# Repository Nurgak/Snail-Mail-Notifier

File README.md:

# Snail Mail Notifier

The Snail Mail Notifier is a small module based on a one-way transmitter-receiver pair and [ATtiny85](http://www.atmel.com/devices/attiny85.aspx) microcontrollers, it's purpose is to inform a user of the arrival of regular mail as soon as the mailbox lid has been opened. The receiver can notify the user via a buzzer, a blinking LED or transmit data to a computer that can forward an e-mail.

[The project development is documented on Hackaday.io](https://hackaday.io/project/1954-snail-mail-notifier).

## License

The Snail Mail Notifier is published under [Creative Commons Attribution license](http://creativecommons.org/licenses/by/3.0/).

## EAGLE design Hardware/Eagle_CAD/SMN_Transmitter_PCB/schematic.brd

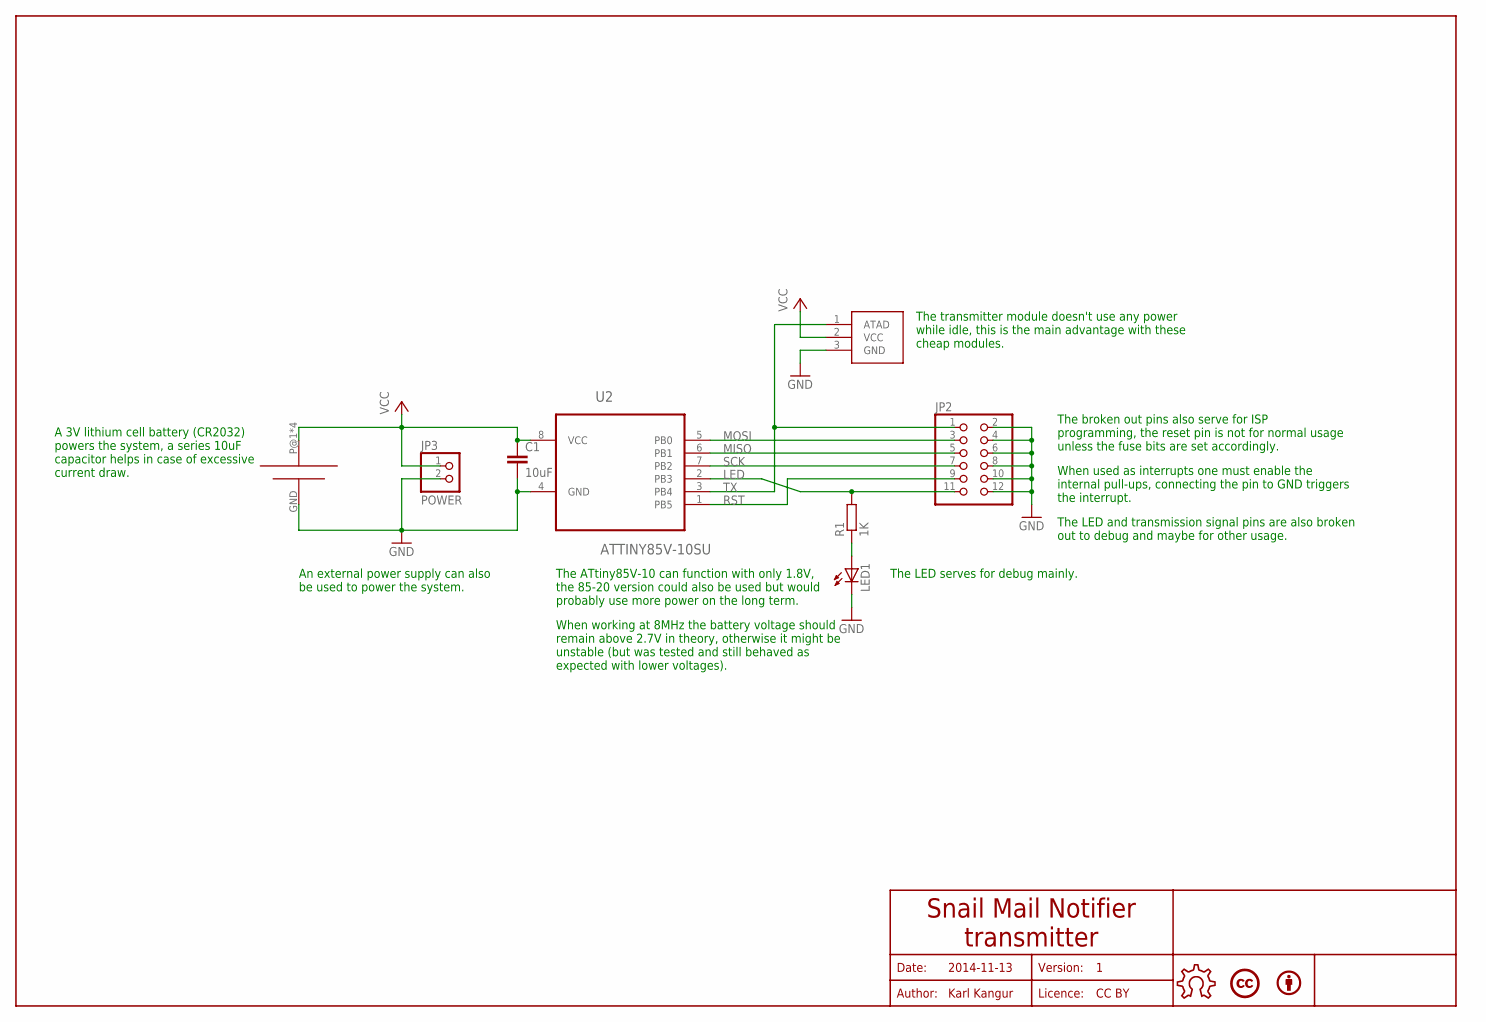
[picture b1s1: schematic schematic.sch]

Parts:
BY1: BYBOTTOM; BY
C1: 10uF; C0805
JP2: PINHD-2X6; 2X06
JP3: POWER; 1X02
LED1: LEDCHIPLED_0805; CHIPLED_0805
LICENCE1: LICENCECC-BOTTOM; CREATIVE-COMMONS
R1: 1K; R0805
U2: ATTINY85V-10SU; SOIC127P798X216-8N
U$1: RF_LINK_TRANSMITTER
U$2: CR2032-BATTERY-HOLDER; CR2032-BATTERY-HOLDER-PCB
U$5: OPEN-HARDWARE-LOGOBOTTOM-SMALL; OPEN-HARDWARE-BOTTOM-SMALL

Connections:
GND: C1.2, JP2.2, JP2.4, JP2.6, JP2.8, JP2.10, JP2.12, JP3.2, LED1.C, U2.4 (GND), U$1.3 (GND), U$2.GND (N)
LED: JP2.11, R1.2, U2.2 (PB3)
MISO: JP2.5, U2.6 (PB1)
MOSI: JP2.3, U2.5 (PB0)
unnamed: LED1.A, R1.1
RST: JP2.9, U2.1 (PB5)
SCK: JP2.7, U2.7 (PB2)
TX: JP2.1, U2.3 (PB4), U$1.1 (ATAD)
VCC: C1.1, JP3.1, U2.8 (VCC), U$1.2 (VCC), U$2.P@1, U$2.P@2, U$2.P@3, U$2.P@4

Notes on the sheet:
Date:
Author:
Licence:
Version:
2014-11-13
Karl Kangur
CC BY
Snail Mail Notifier transmitter
The ATtiny85V-10 can function with only 1.8V, the 85-20 version could also be used but would probably use more power on the long term.
The broken out pins also serve for ISP programming, the reset pin is not for normal usage unless the fuse bits are set accordingly.
A 3V lithium cell battery (CR2032) powers the system, a series 10uF capacitor helps in case of excessive current draw.
An external power supply can also be used to power the system.
The transmitter module doesn't use any power while idle, this is the main advantage with these cheap modules.
When used as interrupts one must enable the internal pull-ups, connecting the pin to GND triggers the interrupt.
The LED serves for debug mainly.
When working at 8MHz the battery voltage should remain above 2.7V in theory, otherwise it might be unstable (but was tested and still behaved as expected with lower voltages).
The LED and transmission signal pins are also broken out to debug and maybe for other usage.

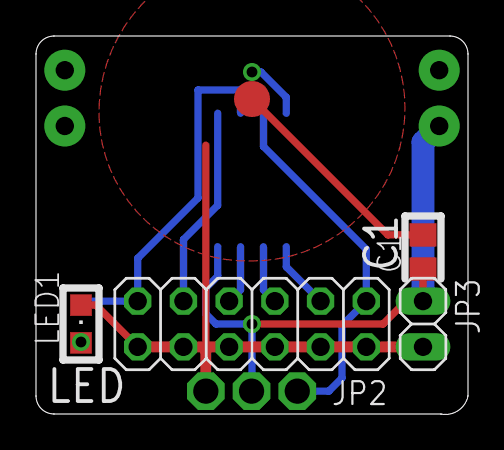
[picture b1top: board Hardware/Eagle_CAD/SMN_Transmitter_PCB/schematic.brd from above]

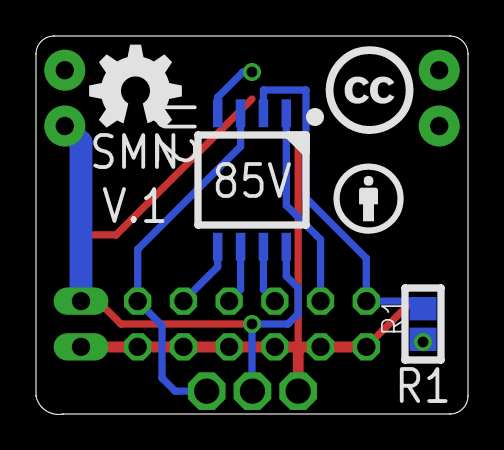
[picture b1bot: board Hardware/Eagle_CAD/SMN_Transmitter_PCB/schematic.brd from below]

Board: 2 copper layers, 24.0 x 21.0 mm, 11 parts (3 on the bottom side), 9 nets.

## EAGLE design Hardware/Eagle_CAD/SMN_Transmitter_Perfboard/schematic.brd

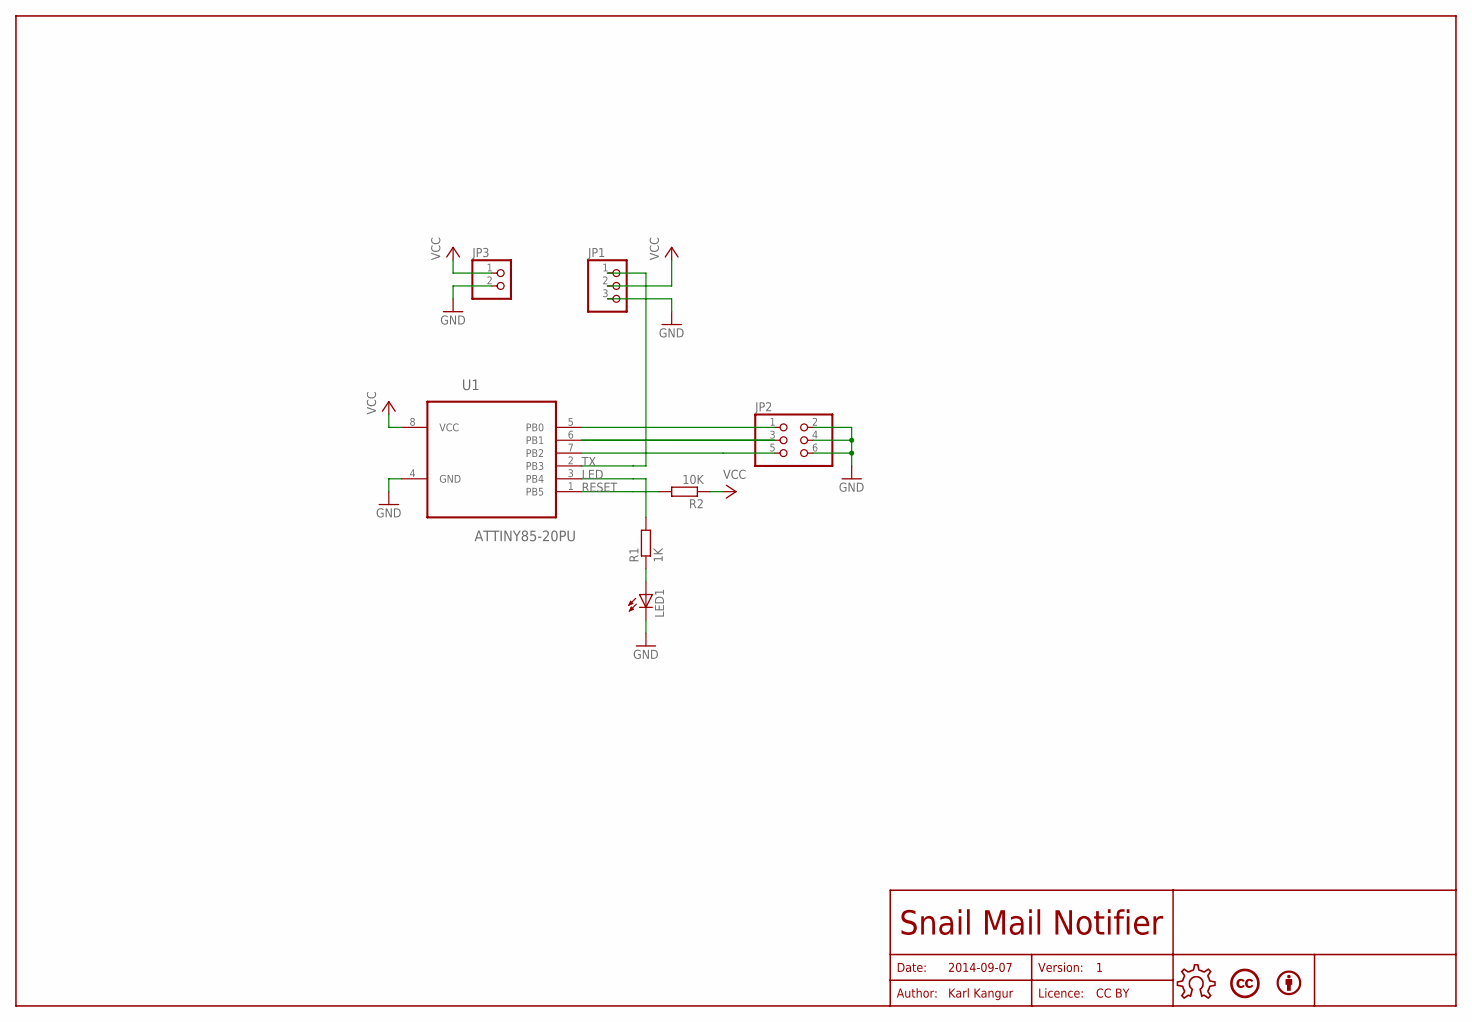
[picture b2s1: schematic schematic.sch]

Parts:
BY1: BYBOTTOM; BY
JP1: PINHD-1X3; 1X03
JP2: PINHD-2X3; 2X03
JP3: PINHD-1X2/90; 1X02/90
LED1: LED3MM
LICENCE1: LICENCECC-BOTTOM; CREATIVE-COMMONS
R1: 1K; R0805
R2: 10K; R0805
U1: ATTINY85-20PU; DIP254P762X533-8
U$5: OPEN-HARDWARE-LOGOBOTTOM-SMALL; OPEN-HARDWARE-BOTTOM-SMALL

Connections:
GND: JP1.3, JP2.2, JP2.4, JP2.6, JP3.2, LED1.K (C)
LED: R1.2, U1.3 (PB4)
unnamed: LED1.A, R1.1
unnamed: JP2.1, U1.5 (PB0)
unnamed: JP2.3, U1.6 (PB1)
unnamed: JP2.5, U1.7 (PB2)
RESET: R2.2, U1.1 (PB5)
TX: JP1.1, U1.2 (PB3)
VCC: JP1.2, JP3.1, R2.1, U1.8 (VCC)

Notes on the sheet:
Date:
Author:
Licence:
Version:
2014-09-07
Karl Kangur
CC BY
Snail Mail Notifier

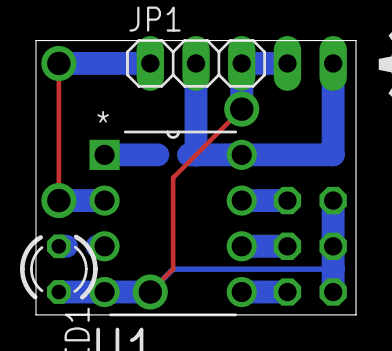
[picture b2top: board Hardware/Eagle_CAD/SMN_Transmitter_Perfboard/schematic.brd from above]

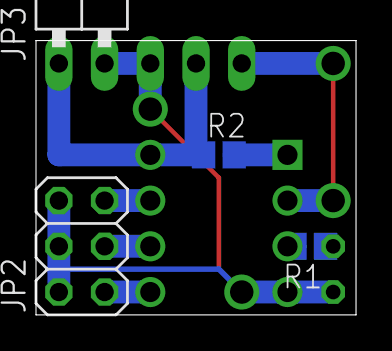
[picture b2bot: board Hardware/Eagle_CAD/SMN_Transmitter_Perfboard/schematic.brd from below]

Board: 2 copper layers, 17.8 x 15.2 mm, 10 parts (7 on the bottom side), 9 nets.

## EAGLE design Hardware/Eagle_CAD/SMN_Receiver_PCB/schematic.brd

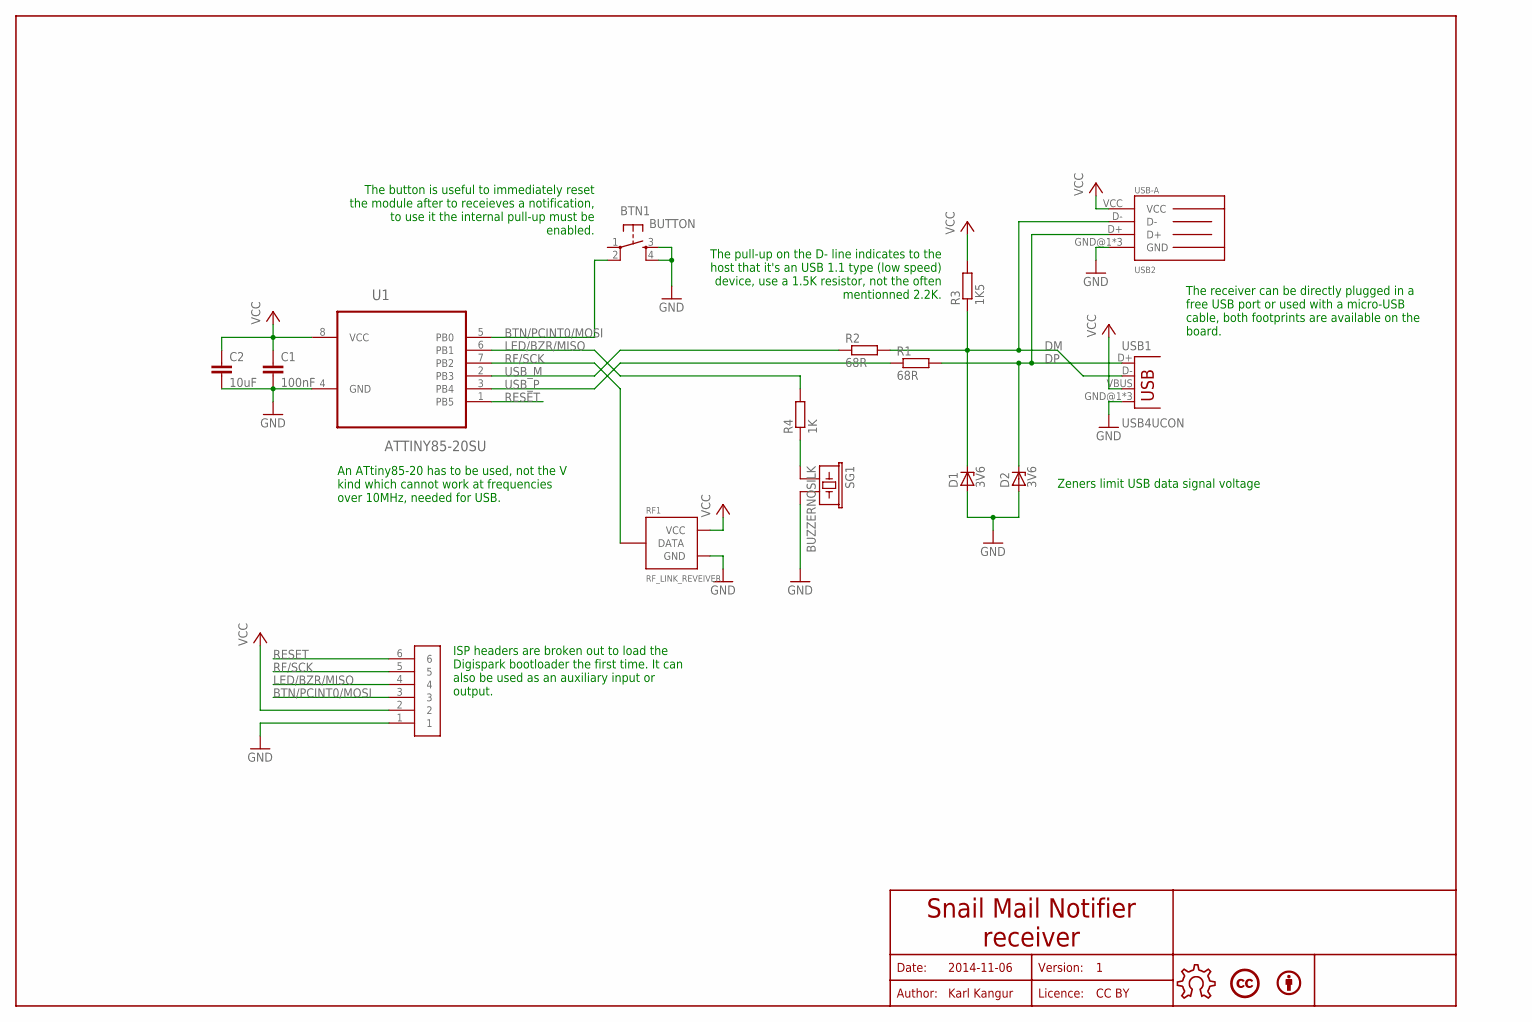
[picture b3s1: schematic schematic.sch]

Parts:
BTN1: BUTTON
BY1: BYBOTTOM; BY
C1: 100nF; C0805
C2: 10uF; C0805
D1, D2: 3V6; SOD80C
LICENCE1: LICENCECC-BOTTOM; CREATIVE-COMMONS
PIN1: PINS-6
R1, R2: 68R; R0805
R3: 1K5; R0805
R4: 1K; R0805
RF1: RF_LINK_REVEIVER
SG1: BUZZERNOSILK; PS1240P02BT-NOSILK
U1: ATTINY85-20SU; SOIC127P798X216-8N
U$5: OPEN-HARDWARE-LOGOBOTTOM-SMALL; OPEN-HARDWARE-BOTTOM-SMALL
USB1: USB4UCON; USB-MICROB-4UCON
USB2: USB-A

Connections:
BTN/PCINT0/MOSI: BTN1.2, PIN1.3, U1.5 (PB0)
DM: D1.C, R2.2, R3.1, USB1.D-, USB2.D-
DP: D2.C, R1.2, USB1.D+, USB2.D+
GND: BTN1.3, BTN1.4, C1.2, C2.2, D1.A, D2.A, PIN1.1, RF1.GND, SG1.P$2 (2), U1.4 (GND), USB1.GND@1 (GND), USB1.GND@4 (GND), USB1.GND@5 (GND), USB2.GND@1 (GND), USB2.GND@2 (GND), USB2.GND@3 (GND)
LED/BZR/MISO: PIN1.4, R4.2, U1.6 (PB1)
unnamed: R4.1, SG1.P$1 (1)
RESET: PIN1.6, U1.1 (PB5)
RF/SCK: PIN1.5, RF1.DATA@1 (DATA), RF1.DATA@2 (DATA), U1.7 (PB2)
USB_M: R2.1, U1.2 (PB3)
USB_P: R1.1, U1.3 (PB4)
VCC: C1.1, C2.1, PIN1.2, R3.2, RF1.VCC, U1.8 (VCC), USB1.VBUS, USB2.VCC

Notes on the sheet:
Date:
Author:
Licence:
Version:
2014-11-06
Karl Kangur
CC BY
Snail Mail Notifier receiver
The receiver can be directly plugged in a free USB port or used with a micro-USB cable, both footprints are available on the board.
Zeners limit USB data signal voltage
The pull-up on the D- line indicates to the host that it's an USB 1.1 type (low speed) device, use a 1.5K resistor, not the often mentionned 2.2K.
The button is useful to immediately reset the module after to receieves a notification, to use it the internal pull-up must be enabled.
An ATtiny85-20 has to be used, not the V kind which cannot work at frequencies over 10MHz, needed for USB.
ISP headers are broken out to load the Digispark bootloader the first time. It can also be used as an auxiliary input or output.

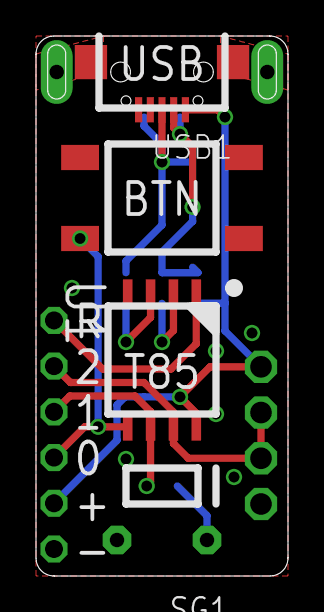
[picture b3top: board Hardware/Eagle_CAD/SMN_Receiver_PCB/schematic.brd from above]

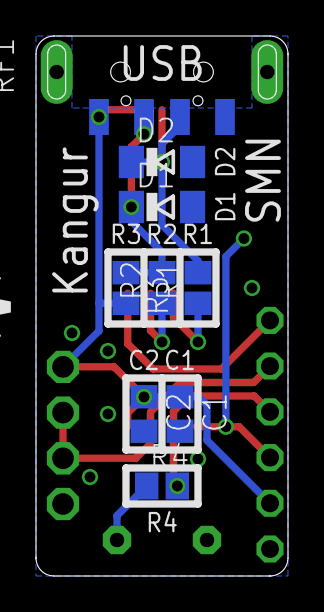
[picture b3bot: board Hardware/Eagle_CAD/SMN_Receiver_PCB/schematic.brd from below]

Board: 2 copper layers, 14.0 x 30.0 mm, 18 parts (12 on the bottom side), 11 nets.

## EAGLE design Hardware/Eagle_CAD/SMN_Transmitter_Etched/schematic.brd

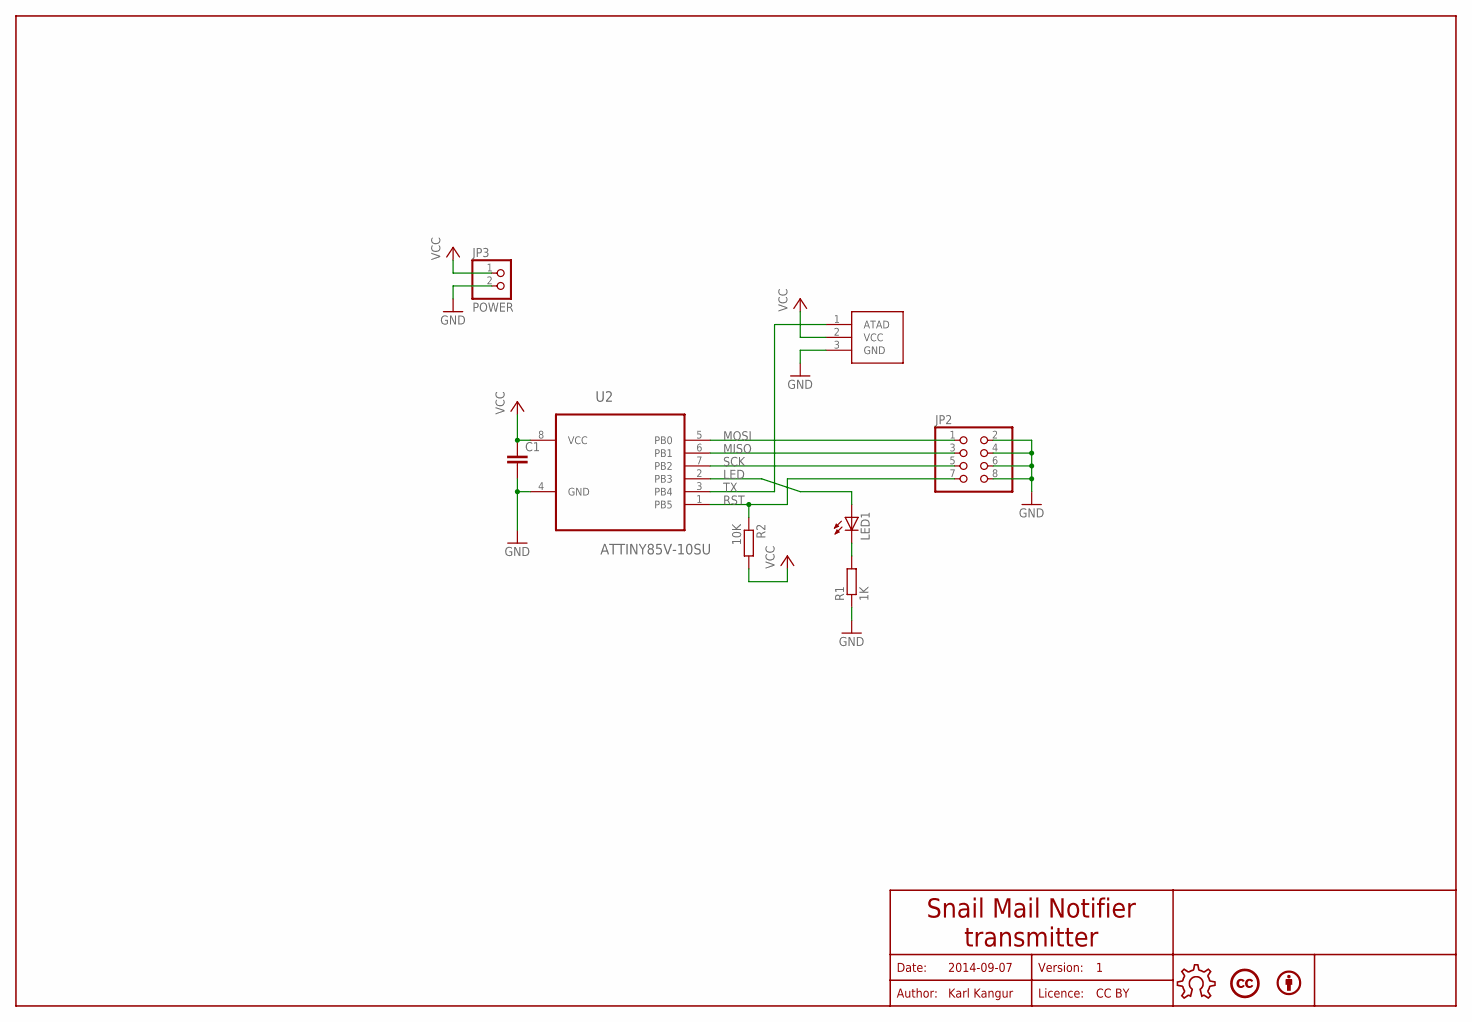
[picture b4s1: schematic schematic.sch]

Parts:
BY1: BYBOTTOM; BY
C1: C-EUC0805; C0805
JP2: PINHD-2X4; 2X04
JP3: POWER; 1X02
LED1: LED3MM
LICENCE1: LICENCECC-BOTTOM; CREATIVE-COMMONS
R1: 1K; R0805
R2: 10K; R0805
U2: ATTINY85V-10SU; SOIC127P798X216-8N
U$1: RF_LINK_TRANSMITTER
U$5: OPEN-HARDWARE-LOGOBOTTOM-SMALL; OPEN-HARDWARE-BOTTOM-SMALL

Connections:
GND: C1.2, JP2.2, JP2.4, JP2.6, JP2.8, JP3.2, R1.1, U2.4 (GND), U$1.3 (GND)
LED: LED1.A, U2.2 (PB3)
MISO: JP2.3, U2.6 (PB1)
MOSI: JP2.1, U2.5 (PB0)
unnamed: LED1.K (C), R1.2
RST: JP2.7, R2.1, U2.1 (PB5)
SCK: JP2.5, U2.7 (PB2)
TX: U2.3 (PB4), U$1.1 (ATAD)
VCC: C1.1, JP3.1, R2.2, U2.8 (VCC), U$1.2 (VCC)

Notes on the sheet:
Date:
Author:
Licence:
Version:
2014-09-07
Karl Kangur
CC BY
Snail Mail Notifier transmitter

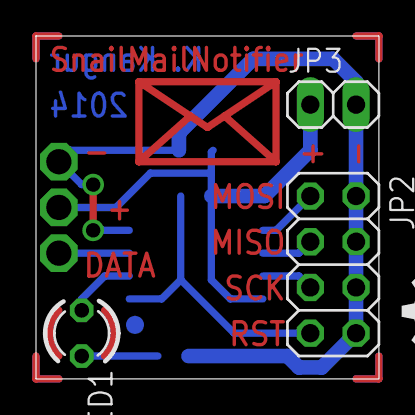
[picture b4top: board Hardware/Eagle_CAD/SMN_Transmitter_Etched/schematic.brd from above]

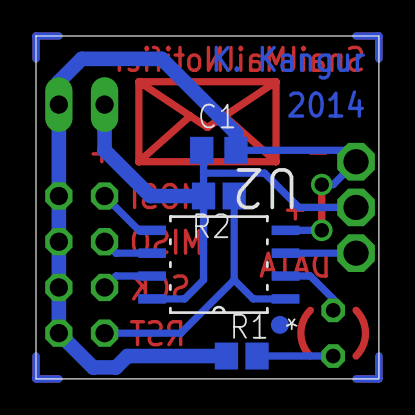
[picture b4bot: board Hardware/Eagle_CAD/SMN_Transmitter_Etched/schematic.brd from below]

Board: 2 copper layers, 19.1 x 19.1 mm, 11 parts (8 on the bottom side), 9 nets.

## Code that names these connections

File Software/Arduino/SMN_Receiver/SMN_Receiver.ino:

/***************************************************************************************
 *
 * Title:       Snail Mail Notifier - Receiver
 * File:        SMN_Receiver.ino
 * Version:     v0.1
 * Date:        2016-01-24
 * Author:      Karl Kangur <karl.kangur@gmail.com>
 * Licence:     CC-BY
 * Website:     https://github.com/Nurgak/Snail-Mail-Notifier
 * Development: https://hackaday.io/project/1954-snail-mail-notifier
 *
 ***************************************************************************************/
#define F_CPU 16500000UL

#include <avr/wdt.h>
#include <VirtualWire.h> // This version of VirtualWire comes with Digispark libraries and has been modified to work with Digispark
#include "DigiKeyboard.h"
#include "pitch.h"
#include "sound.h"

// ATMEL ATTINY85 / ARDUINO / DIGISPARK pinout
//
//                       +-\/-+
//  RST, Ain0 (D5) PB5  1|    |8  Vcc
// USB-, Ain3 (D3) PB3  2|    |7  PB2 (D2) Ain1, PCINT2, INT0, RX
// USB+, Ain2 (D4) PB4  3|    |6  PB1 (D1) PWM1, PCINT1, BUZZER
//                 GND  4|    |5  PB0 (D0) PWM0, PCINT0, BUTTON
//                       +----+

#define KEY_STROKE        KEY_L // Key stroke sent to the computer when a message is receieved
#define MOD_KEYS          MOD_CONTROL_LEFT | MOD_ALT_LEFT | MOD_GUI_LEFT  // Modifier keys such as Ctrl, Alt, Option...
#define SLEEP_MULTIPLIER  450  // Watchdog resets the system when it has been triggered after 450*8s = 3600s = 1h, maximum is 0xfffe
#define BITRATE           200  // Bitrate at which the emitter sends data to the receiver, must be the same on emitter and receiver
#define PIN_BUTTON        0    // Pin definition for button
#define PIN_BUZZER        1    // Pin definition for buzzer
#define PIN_RX            2    // Pin definition for receiver ping
// Pins 3 and 4 are reserved for USB data lines, defined in Digispark libraries

static volatile boolean mail = false; // Volatile as called from within an interrupt vector (resetSystem())
static volatile boolean buttonBusy = false;
static volatile melodyPlay song = {0, STOP, 0, 0, 0, 0}; // Struct to track sound playing

void setup()
{
  // Switch ADC off as it is not needed
  ADCSRA &= ~_BV(ADEN);
    
  // Shut down unused peripherals (USI and ADC)
  PRR |= _BV(PRUSI) | _BV(PRADC);
  
  // Enable button pull-up
  PORTB |= _BV(PIN_BUTTON);
  
  // Receiver initialisation
  vw_set_rx_pin(PIN_RX);
  vw_setup(BITRATE);
  vw_rx_start();
  
  // Watchdog interrupt to reset the system after an hour
  WDTCR = _BV(WDP3) | _BV(WDP0); // Set watchdog timeout to 8s, do not enable yet
}

// Watchdog timeout interrupt vector called every 8s, non blocking since low priority
ISR(WDT_vect, ISR_NOBLOCK)
{
  static uint16_t sleepTimer;

  // Trick to make the countdown internal to the interrupt vector
  if(sleepTimer == 0xffff)
  {
    sleepTimer = SLEEP_MULTIPLIER;
  }
  else
  {
    sleepTimer--;
  }
  
  if(!sleepTimer)
  {
    sleepTimer = 0xffff;
    
    // Disable watchdog, reset system
    WDTCR &= ~_BV(WDIE);
    resetSystem();
  }
}

// Interrupt vector for buzzer sounds, non blocking since low priority
ISR(TIMER0_OVF_vect, ISR_NOBLOCK)
{
  if(song.action == STOP)
  {
    return;
  }
  
  if(song.calls > 0)
  {
    // Decrement call count
    song.calls--;
    // Toggle pin value to make some sound
    PORTB ^= _BV(PIN_BUZZER);
  }
  else if(song.pause > 0)
  {
    // Decrement pause count while not toggling the buzzer pin
    song.pause--;
  }
  else
  {
    // The melody is finished, stop
    if(song.noteCounter == -1)
    {
      song.noteCounter = 0;
      notification(STOP);
      
      // Allow user to push the button again
      buttonBusy = false;
      
      return;
    }
    
    // Evaluate timeout value for the given sound freqency, one has to use the timeout interrupt vector as the overflow won't work
    // The timeout vector is always called at TOP = 0xff in CTC mode so simply set an offset to the timer 0 counter register: TCNT0
    // TCNT0 = 0xff - (16.5MHz / 1024 / 2 / frequency)
    song.nextCall = 0xff - ((F_CPU >> 11) / song.reference->notes[song.noteCounter].pitch);
    
    // If the frequency of the current sound is the same as the next one insert a 5ms pause at the end of the note duration to define the notes better
    if(song.noteCounter < song.reference->length - 2 && song.reference->notes[song.noteCounter].pitch == song.reference->notes[song.noteCounter + 1].pitch)
    {
      // The casting is necessary or it won't behave as expected
      // The division is by 500 instead of 1000 because the pin is toggeled instead of making a full period per interrupt call, so there are twice the number of cycles
      song.calls = ((uint32_t) song.reference->notes[song.noteCounter].pitch * (song.reference->notes[song.noteCounter].duration - 5)) / 500;
      // Insert a 5ms pause at the end of the sound
      song.pause = (song.reference->notes[song.noteCounter].pitch * 5) / 500;
    }
    else
    {
      // Evaluate call count for given frequency
      song.calls = ((uint32_t) song.reference->notes[song.noteCounter].pitch * song.reference->notes[song.noteCounter].duration) / 500;
    }
    
    if(song.noteCounter < song.reference->length - 1)
    {
      // Evaluate calls for the next frequency
      song.noteCounter++;
    }
    else
    {
      // End of the song, stop
      song.noteCounter = -1;
    }
  }
  
  // Set the counter register to a set value so it would trigger this interrupt next time
  TCNT0 = song.nextCall;
}

void loop()
{
  // Buffer for the received message
  static uint8_t buf[5] = {0};
  static uint8_t buflen = sizeof(buf) / sizeof(buf[0]);

  // Received data variables
  static uint8_t address = 0;
  static uint16_t voltage = 0;
  static uint8_t temperature = 0;
  static uint8_t data = 0; // Dummy data, should be 0x55 by default

  // The receiver can only receieve a message when not playing a notification as they use the same timer
  if(song.action == STOP && !mail && vw_get_message(buf, &buflen))
  {
    // Fill the values
    address = buf[0];
    voltage = (buf[1] << 8) | buf[2];
    temperature = buf[3];
    data = buf[4];

    // Send the key stroke to the computer
    DigiKeyboard.sendKeyStroke(KEY_STROKE, MOD_KEYS);
    
    // Toggle mail flag
    mail = true;

    // Enable watchdog timeout (WDT_vect) interrupt
    wdt_reset();
    WDTCR |= _BV(WDIE);
    
    selectMelody(&melodyNewMail);
  }
  
  // Button was pressed, cannot use the interrupt vector as the DigiKeyboard library needs it, so poll instead
  if(!(PINB & _BV(PIN_BUTTON)) && !buttonBusy)
  {
    button();
  }
  
  // Wait 1ms and fill the time with USB polling to indicate to the computer that the device has not disappeared
  DigiKeyboard.delay(1);
}

void button()
{
  // The user can reset the system by pushing on the button
  resetSystem();
  
  // The user could be holding the button down, prevent calling this multiple times
  buttonBusy = true;
  selectMelody(&melodyButtonPush);
}

void selectMelody(const melody * _melody)
{
  // Select the melody to play by setting the references to the sound and its length
  song.reference = (melody *)_melody;
    
  // Enable notification so the buzzer would play
  notification(PLAY);
}

// Setup the buzzer to notify user of arrived mail
void notification(operation action)
{
  // Save timer 0 configuration, since the receiver uses the same timer as the buzzer
  static uint8_t temp_TCCR0A = TCCR0A;
  static uint8_t temp_TCCR0B = TCCR0B;
  static uint8_t temp_OCR0A = OCR0A;
  static uint8_t temp_TIMSK = TIMSK;
  
  if(action == PLAY)
  {
    // Set buzzer pin to output
    DDRB |= _BV(PIN_BUZZER);
    
    // Reset sound generation variables
    song.calls = 0;
    song.pause = 0;
    song.nextCall = 0;
    song.noteCounter = 0;
    
    TCCR0A = _BV(WGM01); // CTC mode
    OCR0A = 0xff; // Count up to 0xff to trigger the overflow interrupt vector
    TIMSK |= _BV(TOIE0); // Enable the overflow (TIMER0_OVF_vect) interrupt vector to change frequency
    TCCR0B = _BV(CS02) | _BV(CS00); // Prescaler = 1024
  }
  else
  {
    // Restore timer 0 configuration
    TCCR0A = temp_TCCR0A;
    TCCR0B = temp_TCCR0B;
    OCR0A = temp_OCR0A;
    TIMSK = temp_TIMSK;
    
    // Set buzzer pin off and to input mode
    PORTB &= ~_BV(PIN_BUZZER);
    DDRB &= ~_BV(PIN_BUZZER);
  }
  
  song.action = action;
}

void resetSystem()
{
  // Disable watchdog interrupt for automatic reset (not actual MCU reset, only program reset)
  WDTCR |= _BV(WDIE);
  
  // Turn off the notification
  notification(STOP);
  
  // Remove mail flag
  mail = false;
}

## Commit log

2016-01-31 Added a picture
